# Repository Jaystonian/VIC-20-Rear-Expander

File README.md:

# VIC-20-Rear-Expander
A full-featured, powered and protected expansion motherboard for the Commodore VIC-20

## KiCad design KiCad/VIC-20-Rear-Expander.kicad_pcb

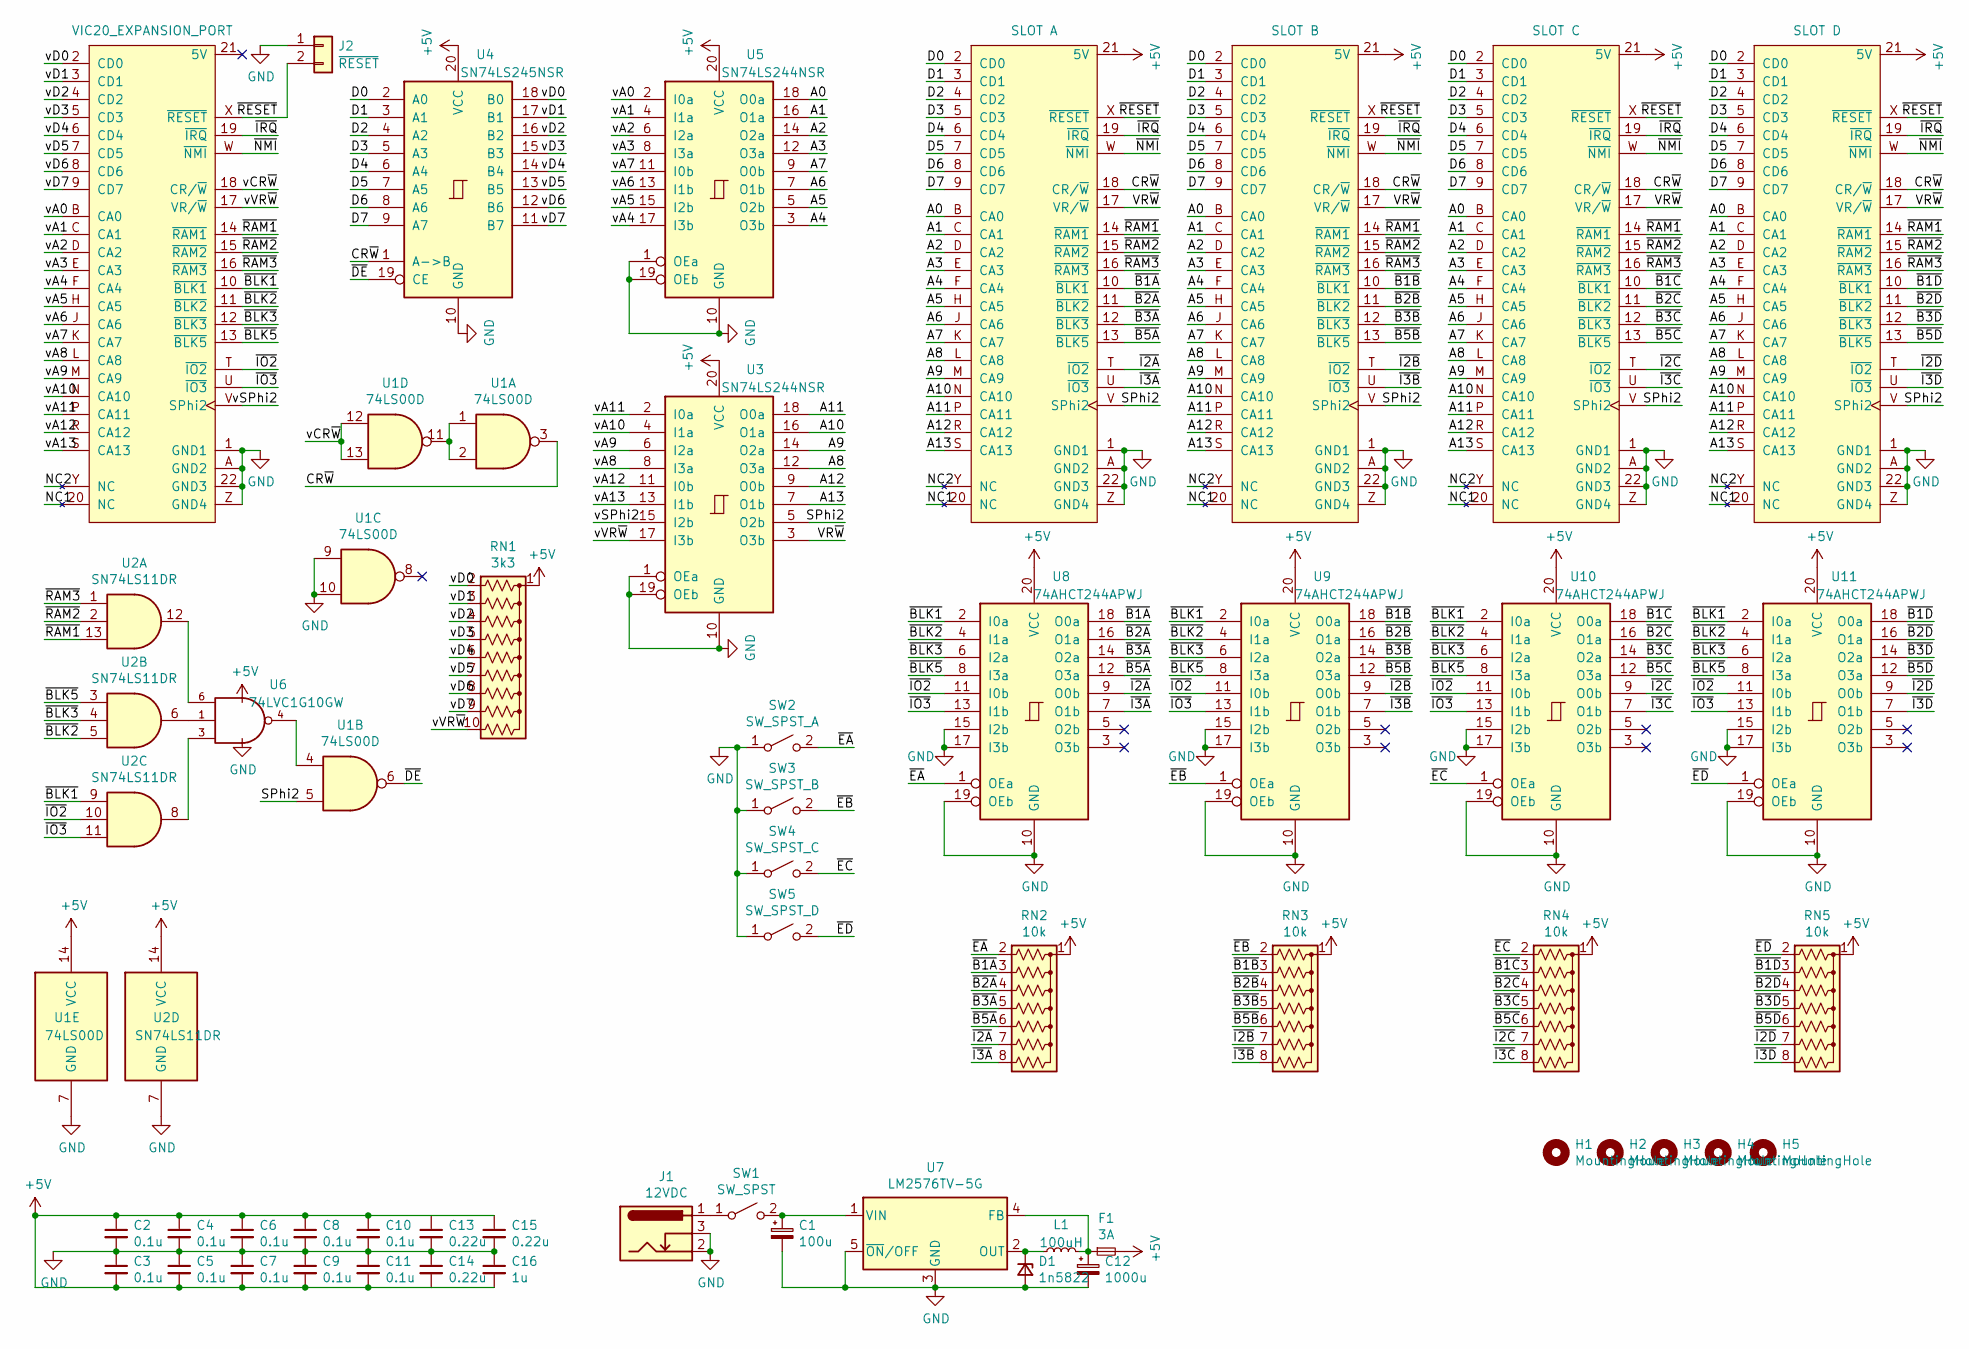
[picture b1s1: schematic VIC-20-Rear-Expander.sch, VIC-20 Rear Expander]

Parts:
C1: 100u; CP_Radial_D10.0mm_P5.00mm
C2, C3, C4, C5, C6, C7, C8, C9, C10, C11: 0.1u; C_0603_1608Metric_Pad1.05x0.95mm_HandSolder
C12: 1000u; CP_Radial_D10.0mm_P5.00mm
C13: 0.22u; C_0805_2012Metric_Pad1.18x1.45mm_HandSolder
C14, C15: 0.22u; C_0805_2012Metric_Pad1.15x1.40mm_HandSolder
C16: 1u; C_0805_2012Metric_Pad1.15x1.40mm_HandSolder
D1: 1n5822; D_DO-201AD_P15.24mm_Horizontal
F1: 3A; FUSE_5x20mm-2x00300210H
H1, H2, H3, H4, H5: MountingHole; MountingHole_3.2mm_M3_Pad_Via
J1: 12VDC; BarrelJack_Wuerth_6941xx301002
J2: ~RESET; PinHeader_1x02_P2.54mm_Vertical
L1: 100uH; L_Bourns_SDR1806
RN1: 3k3; R_Array_SIP10
RN2, RN3, RN4, RN5: 10k; R_Array_SIP8
SW1: SW_SPST; Molex_KK-396_A-41791-0002_1x02_P3.96mm_Vertical
SW2: SW_SPST_A; PinHeader_1x02_P2.54mm_Vertical
SW3: SW_SPST_B; PinHeader_1x02_P2.54mm_Vertical
SW4: SW_SPST_C; PinHeader_1x02_P2.54mm_Vertical
SW5: SW_SPST_D; PinHeader_1x02_P2.54mm_Vertical
U1: 74LS00D; SOIC-14_3.9x8.7mm_P1.27mm
U2: SN74LS11DR; SOIC-14_3.9x8.7mm_P1.27mm
U3, U5: SN74LS244NSR; SOP-20_7.5x12.8mm_P1.27mm
U4: SN74LS245NSR; SOP-20_7.5x12.8mm_P1.27mm
U6: 74LVC1G10GW; SOT-363_SC-70-6
U7: LM2576TV-5G; TO-220-5_Vertical
U8, U9, U10, U11: 74AHCT244APWJ; TSSOP-20_4.4x6.5mm_P0.65mm
X1: VIC20_EXPANSION_PORT; VIC20_EXPANSION_CARD_3
X2: SLOT A; VIC20_EXPANSIONPORT_WIRE
X3: SLOT B; VIC20_EXPANSIONPORT_WIRE
X4: SLOT C; VIC20_EXPANSIONPORT_WIRE
X5: SLOT D; VIC20_EXPANSIONPORT_WIRE

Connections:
+5V: C2.1, C3.2, C4.1, C5.2, C6.1, C7.2, C8.1, C9.2, C10.1, C11.2, C13.1, C14.2, C15.1, C16.2, F1.2, RN1.1 (common), RN2.1 (common), RN3.1 (common), RN4.1 (common), RN5.1 (common), U1.14 (VCC), U2.14 (VCC), U3.20 (VCC), U4.20 (VCC), U5.20 (VCC), U6.5 (VCC), U8.20 (VCC), U9.20 (VCC), U10.20 (VCC), U11.20 (VCC), X2.21 (5V), X3.21 (5V), X4.21 (5V), X5.21 (5V)
/A0: U5.18 (O0a), X2.B (CA0), X3.B (CA0), X4.B (CA0), X5.B (CA0)
/A1: U5.16 (O1a), X2.C (CA1), X3.C (CA1), X4.C (CA1), X5.C (CA1)
/A2: U5.14 (O2a), X2.D (CA2), X3.D (CA2), X4.D (CA2), X5.D (CA2)
/A3: U5.12 (O3a), X2.E (CA3), X3.E (CA3), X4.E (CA3), X5.E (CA3)
/A4: U5.3 (O3b), X2.F (CA4), X3.F (CA4), X4.F (CA4), X5.F (CA4)
/A5: U5.5 (O2b), X2.H (CA5), X3.H (CA5), X4.H (CA5), X5.H (CA5)
/A6: U5.7 (O1b), X2.J (CA6), X3.J (CA6), X4.J (CA6), X5.J (CA6)
/A7: U5.9 (O0b), X2.K (CA7), X3.K (CA7), X4.K (CA7), X5.K (CA7)
/A8: U3.12 (O3a), X2.L (CA8), X3.L (CA8), X4.L (CA8), X5.L (CA8)
/A9: U3.14 (O2a), X2.M (CA9), X3.M (CA9), X4.M (CA9), X5.M (CA9)
/A10: U3.16 (O1a), X2.N (CA10), X3.N (CA10), X4.N (CA10), X5.N (CA10)
/A11: U3.18 (O0a), X2.P (CA11), X3.P (CA11), X4.P (CA11), X5.P (CA11)
/A12: U3.9 (O0b), X2.R (CA12), X3.R (CA12), X4.R (CA12), X5.R (CA12)
/A13: U3.7 (O1b), X2.S (CA13), X3.S (CA13), X4.S (CA13), X5.S (CA13)
/CR~W: U1.3, U4.1 (A->B), X2.18 (CR/~W~), X3.18 (CR/~W~), X4.18 (CR/~W~), X5.18 (CR/~W~)
/D0: U4.2 (A0), X2.2 (CD0), X3.2 (CD0), X4.2 (CD0), X5.2 (CD0)
/D1: U4.3 (A1), X2.3 (CD1), X3.3 (CD1), X4.3 (CD1), X5.3 (CD1)
/D2: U4.4 (A2), X2.4 (CD2), X3.4 (CD2), X4.4 (CD2), X5.4 (CD2)
/D3: U4.5 (A3), X2.5 (CD3), X3.5 (CD3), X4.5 (CD3), X5.5 (CD3)
/D4: U4.6 (A4), X2.6 (CD4), X3.6 (CD4), X4.6 (CD4), X5.6 (CD4)
/D5: U4.7 (A5), X2.7 (CD5), X3.7 (CD5), X4.7 (CD5), X5.7 (CD5)
/D6: U4.8 (A6), X2.8 (CD6), X3.8 (CD6), X4.8 (CD6), X5.8 (CD6)
/D7: U4.9 (A7), X2.9 (CD7), X3.9 (CD7), X4.9 (CD7), X5.9 (CD7)
/NC1: X1.20 (NC), X2.20 (NC), X3.20 (NC), X4.20 (NC), X5.20 (NC)
/NC2: X1.Y (NC), X2.Y (NC), X3.Y (NC), X4.Y (NC), X5.Y (NC)
/SPhi2: U1.5, U3.5 (O2b), X2.V (SPhi2), X3.V (SPhi2), X4.V (SPhi2), X5.V (SPhi2)
/VR~W: U3.3 (O3b), X2.17 (VR/~W~), X3.17 (VR/~W~), X4.17 (VR/~W~), X5.17 (VR/~W~)
/vA0: U5.2 (I0a), X1.B (CA0)
/vA1: U5.4 (I1a), X1.C (CA1)
/vA2: U5.6 (I2a), X1.D (CA2)
/vA3: U5.8 (I3a), X1.E (CA3)
/vA4: U5.17 (I3b), X1.F (CA4)
/vA5: U5.15 (I2b), X1.H (CA5)
/vA6: U5.13 (I1b), X1.J (CA6)
/vA7: U5.11 (I0b), X1.K (CA7)
/vA8: U3.8 (I3a), X1.L (CA8)
/vA9: U3.6 (I2a), X1.M (CA9)
/vA10: U3.4 (I1a), X1.N (CA10)
/vA11: U3.2 (I0a), X1.P (CA11)
/vA12: U3.11 (I0b), X1.R (CA12)
/vA13: U3.13 (I1b), X1.S (CA13)
/vCR~W: U1.12, U1.13, X1.18 (CR/~W~)
/vD0: RN1.2 (R1), U4.18 (B0), X1.2 (CD0)
/vD1: RN1.3 (R2), U4.17 (B1), X1.3 (CD1)
/vD2: RN1.4 (R3), U4.16 (B2), X1.4 (CD2)
/vD3: RN1.5 (R4), U4.15 (B3), X1.5 (CD3)
/vD4: RN1.6 (R5), U4.14 (B4), X1.6 (CD4)
/vD5: RN1.7 (R6), U4.13 (B5), X1.7 (CD5)
/vD6: RN1.8 (R7), U4.12 (B6), X1.8 (CD6)
/vD7: RN1.9 (R8), U4.11 (B7), X1.9 (CD7)
/vSPhi2: U3.15 (I2b), X1.V (SPhi2)
/vVR~W: RN1.10 (R9), U3.17 (I3b), X1.17 (VR/~W~)
/~B1A: RN2.3 (R2), U8.18 (O0a), X2.10 (~BLK1~)
/~B1B: RN3.3 (R2), U9.18 (O0a), X3.10 (~BLK1~)
/~B1C: RN4.3 (R2), U10.18 (O0a), X4.10 (~BLK1~)
/~B1D: RN5.3 (R2), U11.18 (O0a), X5.10 (~BLK1~)
/~B2A: RN2.4 (R3), U8.16 (O1a), X2.11 (~BLK2~)
/~B2B: RN3.4 (R3), U9.16 (O1a), X3.11 (~BLK2~)
/~B2C: RN4.4 (R3), U10.16 (O1a), X4.11 (~BLK2~)
/~B2D: RN5.4 (R3), U11.16 (O1a), X5.11 (~BLK2~)
/~B3A: RN2.5 (R4), U8.14 (O2a), X2.12 (~BLK3~)
/~B3B: RN3.5 (R4), U9.14 (O2a), X3.12 (~BLK3~)
/~B3C: RN4.5 (R4), U10.14 (O2a), X4.12 (~BLK3~)
/~B3D: RN5.5 (R4), U11.14 (O2a), X5.12 (~BLK3~)
/~B5A: RN2.6 (R5), U8.12 (O3a), X2.13 (~BLK5~)
/~B5B: RN3.6 (R5), U9.12 (O3a), X3.13 (~BLK5~)
/~B5C: RN4.6 (R5), U10.12 (O3a), X4.13 (~BLK5~)
/~B5D: RN5.6 (R5), U11.12 (O3a), X5.13 (~BLK5~)
/~BLK1: U2.9, U8.2 (I0a), U9.2 (I0a), U10.2 (I0a), U11.2 (I0a), X1.10 (~BLK1~)
/~BLK2: U2.5, U8.4 (I1a), U9.4 (I1a), U10.4 (I1a), U11.4 (I1a), X1.11 (~BLK2~)
/~BLK3: U2.4, U8.6 (I2a), U9.6 (I2a), U10.6 (I2a), U11.6 (I2a), X1.12 (~BLK3~)
/~BLK5: U2.3, U8.8 (I3a), U9.8 (I3a), U10.8 (I3a), U11.8 (I3a), X1.13 (~BLK5~)
/~DE: U1.6, U4.19 (CE)
/~EA: RN2.2 (R1), SW2.2 (B), U8.1 (OEa)
/~EB: RN3.2 (R1), SW3.2 (B), U9.1 (OEa)
/~EC: RN4.2 (R1), SW4.2 (B), U10.1 (OEa)
/~ED: RN5.2 (R1), SW5.2 (B), U11.1 (OEa)
/~I2A: RN2.7 (R6), U8.9 (O0b), X2.T (~IO2)
/~I2B: RN3.7 (R6), U9.9 (O0b), X3.T (~IO2)
/~I2C: RN4.7 (R6), U10.9 (O0b), X4.T (~IO2)
/~I2D: RN5.7 (R6), U11.9 (O0b), X5.T (~IO2)
/~I3A: RN2.8 (R7), U8.7 (O1b), X2.U (~IO3)
/~I3B: RN3.8 (R7), U9.7 (O1b), X3.U (~IO3)
/~I3C: RN4.8 (R7), U10.7 (O1b), X4.U (~IO3)
/~I3D: RN5.8 (R7), U11.7 (O1b), X5.U (~IO3)
/~IO2: U2.10, U8.11 (I0b), U9.11 (I0b), U10.11 (I0b), U11.11 (I0b), X1.T (~IO2)
/~IO3: U2.11, U8.13 (I1b), U9.13 (I1b), U10.13 (I1b), U11.13 (I1b), X1.U (~IO3)
/~IRQ: X1.19 (~IRQ~), X2.19 (~IRQ~), X3.19 (~IRQ~), X4.19 (~IRQ~), X5.19 (~IRQ~)
/~NMI: X1.W (~NMI~), X2.W (~NMI~), X3.W (~NMI~), X4.W (~NMI~), X5.W (~NMI~)
/~RAM1: U2.13, X1.14 (~RAM1~), X2.14 (~RAM1~), X3.14 (~RAM1~), X4.14 (~RAM1~), X5.14 (~RAM1~)
/~RAM2: U2.2, X1.15 (~RAM2~), X2.15 (~RAM2~), X3.15 (~RAM2~), X4.15 (~RAM2~), X5.15 (~RAM2~)
/~RAM3: U2.1, X1.16 (~RAM3~), X2.16 (~RAM3~), X3.16 (~RAM3~), X4.16 (~RAM3~), X5.16 (~RAM3~)
/~RESET: J2.2, X1.X (~RESET~), X2.X (~RESET~), X3.X (~RESET~), X4.X (~RESET~), X5.X (~RESET~)
GND: C1.2, C2.2, C3.1, C4.2, C5.1, C6.2, C7.1, C8.2, C9.1, C10.2, C11.1, C12.2, C13.2, C14.1, C15.2, C16.1, D1.2 (A), J1.2, J1.3, J2.1, SW2.1 (A), SW3.1 (A), SW4.1 (A), SW5.1 (A), U1.7 (GND), U1.9, U1.10, U2.7 (GND), U3.1 (OEa), U3.10 (GND), U3.19 (OEb), U4.10 (GND), U5.1 (OEa), U5.10 (GND), U5.19 (OEb), U6.2 (GND), U7.3 (GND), U7.5 (~ON~/OFF), U8.10 (GND), U8.15 (I2b), U8.17 (I3b), U8.19 (OEb), U9.10 (GND), U9.15 (I2b), U9.17 (I3b), U9.19 (OEb), U10.10 (GND), U10.15 (I2b), U10.17 (I3b), U10.19 (OEb), U11.10 (GND), U11.15 (I2b), U11.17 (I3b), U11.19 (OEb), X1.1 (GND1), X1.22 (GND3), X1.A (GND2), X1.Z (GND4), X2.1 (GND1), X2.22 (GND3), X2.A (GND2), X2.Z (GND4), X3.1 (GND1), X3.22 (GND3), X3.A (GND2), X3.Z (GND4), X4.1 (GND1), X4.22 (GND3), X4.A (GND2), X4.Z (GND4), X5.1 (GND1), X5.22 (GND3), X5.A (GND2), X5.Z (GND4)
unnamed: C1.1, SW1.2 (B), U7.1 (VIN)
unnamed: C12.1, F1.1, L1.2, U7.4 (FB)
unnamed: D1.1 (K), L1.1, U7.2 (OUT)
unnamed: J1.1, SW1.1 (A)
unnamed: U1.1, U1.2, U1.11
unnamed: U1.4, U6.4
unnamed: U2.6, U6.1
unnamed: U2.8, U6.3
unnamed: U2.12, U6.6

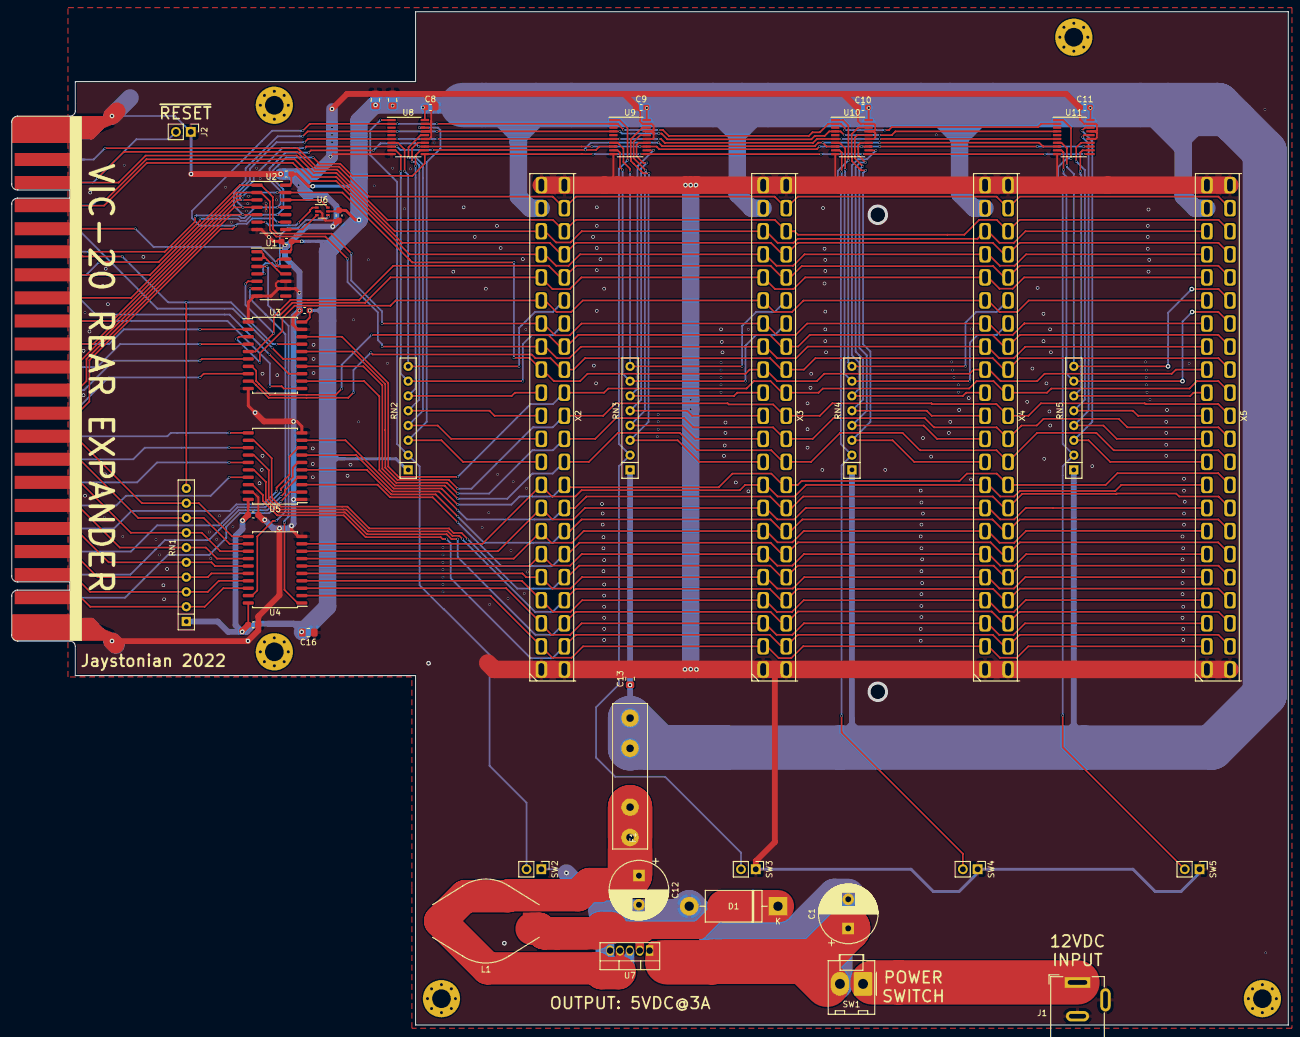
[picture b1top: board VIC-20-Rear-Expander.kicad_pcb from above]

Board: 2 copper layers, 219.2 x 174.0 mm, 52 parts (0 on the bottom side), 104 nets.
